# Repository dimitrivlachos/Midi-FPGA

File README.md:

# Midi-FPGA
 My custom FPGA for a project box I have been using

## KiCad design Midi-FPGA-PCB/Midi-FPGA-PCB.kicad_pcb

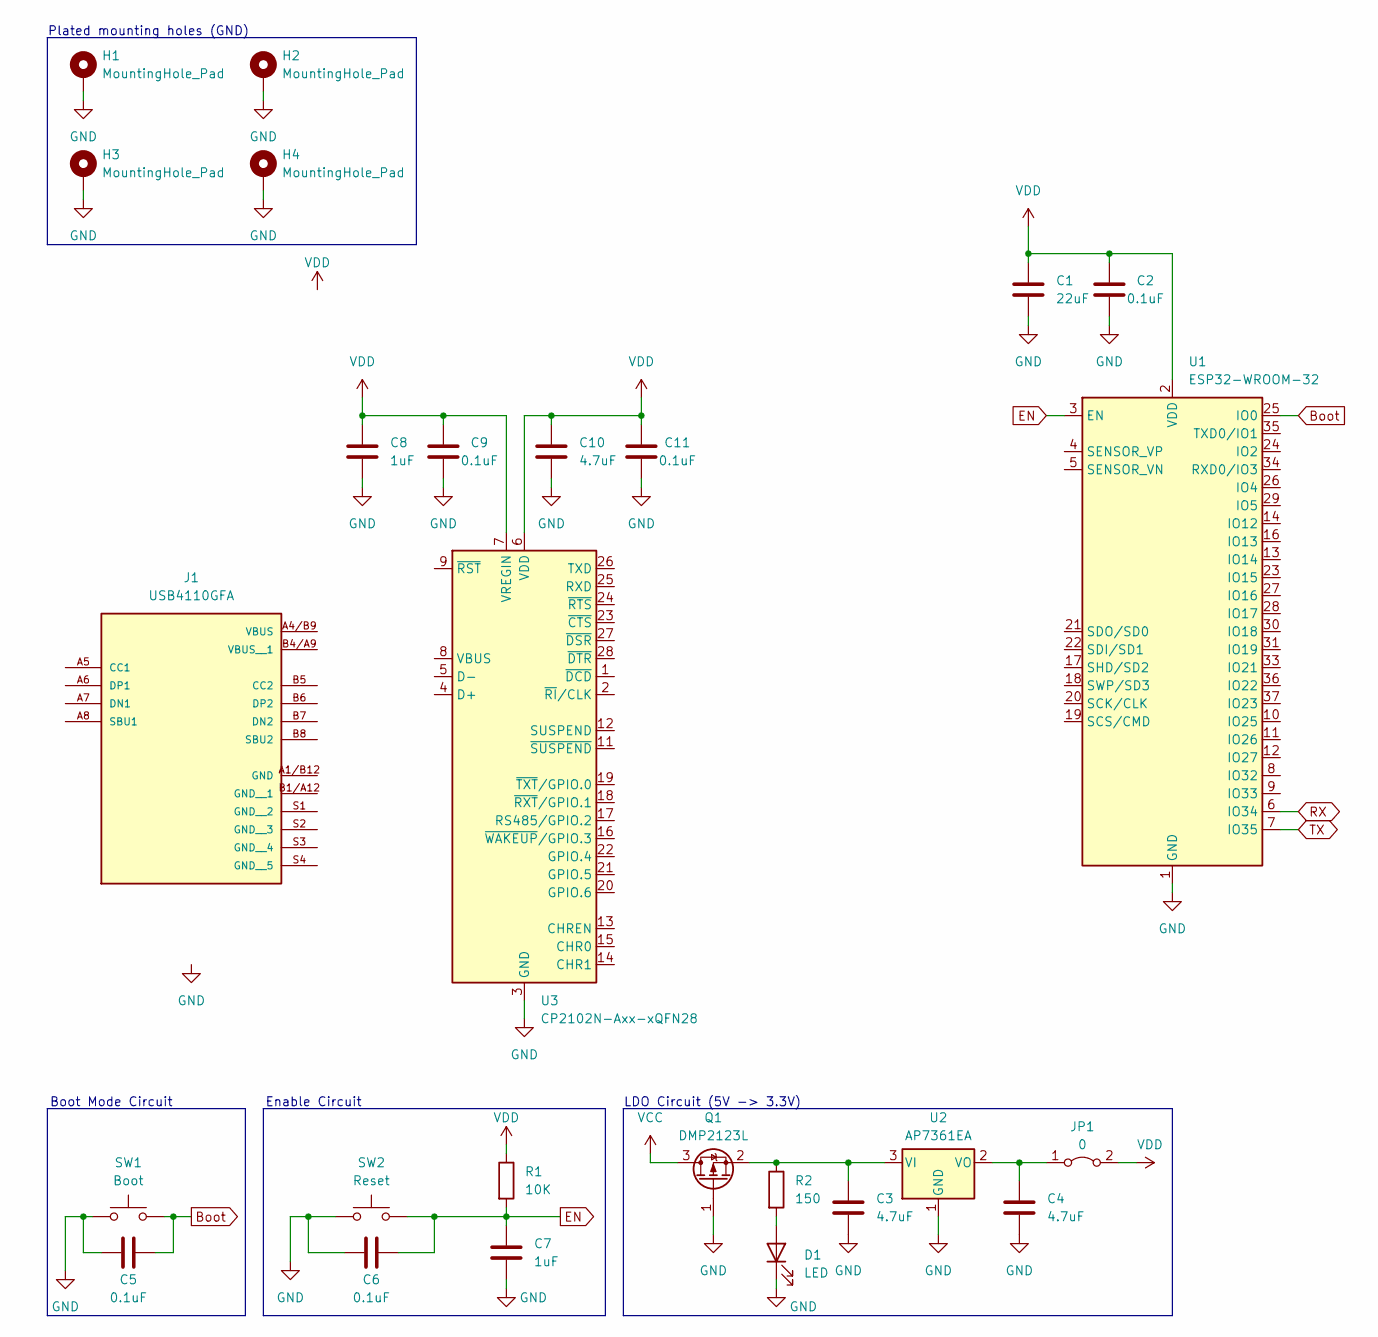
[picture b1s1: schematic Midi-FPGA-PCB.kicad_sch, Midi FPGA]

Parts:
C1: 22uF; C_0805_2012Metric_Pad1.18x1.45mm_HandSolder
C2, C5, C6, C9, C11: 0.1uF; C_0805_2012Metric_Pad1.18x1.45mm_HandSolder
C3, C4, C10: 4.7uF; C_0805_2012Metric_Pad1.18x1.45mm_HandSolder
C7, C8: 1uF; C_0805_2012Metric_Pad1.18x1.45mm_HandSolder
D1: LED; LED_0603_1608Metric_Pad1.05x0.95mm_HandSolder
H1, H2, H3, H4: MountingHole_Pad; MountingHole_2.2mm_M2_DIN965_Pad
J1: USB4110GFA; GCT_USB4110GFA
JP1: 0; R_0805_2012Metric_Pad1.20x1.40mm_HandSolder
Q1: DMP2123L; SOT-23-3
R1: 10K; R_0805_2012Metric_Pad1.20x1.40mm_HandSolder
R2: 150; R_0805_2012Metric_Pad1.20x1.40mm_HandSolder
SW1: Boot
SW2: Reset
U1: ESP32-WROOM-32
U2: AP7361EA; SOT-223-3R
U3: CP2102N-Axx-xQFN28; QFN-28-1EP_5x5mm_P0.5mm_EP3.35x3.35mm

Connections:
Boot: C5.2, SW1.2, U1.25 (IO0)
EN: C6.2, C7.1, R1.2, SW2.2, U1.3 (EN)
GND: C1.2, C2.1, C3.2, C4.2, C5.1, C6.1, C7.2, C8.2, C9.1, C10.2, C11.1, D1.1 (K), H1.1, H2.1, H3.1, H4.1, Q1.1 (G), SW1.1, SW2.1, U1.1 (GND), U1.15 (GND), U1.38 (GND), U1.39 (GND), U2.1 (GND), U3.3 (GND), U3.29 (GND)
unnamed: D1.2 (A), R2.2
unnamed: C4.1, JP1.1 (A), U2.2 (VO)
unnamed: C3.1, Q1.2 (S), R2.1, U2.3 (VI)
RX: U1.6 (IO34)
TX: U1.7 (IO35)
VCC: Q1.3 (D)
VDD: C1.1, C2.2, C8.1, C9.2, C10.1, C11.2, JP1.2 (B), R1.1, U1.2 (VDD), U3.6 (VDD), U3.7 (VREGIN)

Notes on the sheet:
Boot Mode Circuit
Plated mounting holes (GND)
LDO Circuit (5V -> 3.3V)
Enable Circuit

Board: 4 copper layers, 24 parts (0 on the bottom side), 7 nets, no tracks yet.

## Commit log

2023-11-07 Created base gitignore
2023-11-07 Created KiCad Project
2023-11-08 Added custom rules and mounting holes
2023-11-08 Converted board to four layer board
2023-11-08 Created board outline
2023-11-08 Added ground plane fill
2023-11-08 Added title, date and revision to pcb
2023-11-08 Boxed schematic
2023-11-08 Closed programs
2023-11-08 Added ignore to folder access files
2023-11-08 Arranged and documented
2023-11-08 Placed ESP32
2023-11-08 ESP32 placement
2023-11-08 Added ground fills
2023-11-08 Created LDO circuit
2023-11-09 Created LDO circuitry
2023-11-09 Created enable circuit
2023-11-09 Named reset switch
2023-11-09 Finished power and enable circuitry
2023-11-09 Created boot mode circuit
2023-11-09 Reset annotations
2023-11-09 Added RX and TX nets
2023-11-16 Added USB circuit
2023-11-17 Added custom usb c library
